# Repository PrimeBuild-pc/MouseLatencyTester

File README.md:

<div align="center">

<br>

<br>

**Measure how long your mouse actually takes to click — to the microsecond.**

A Teensy 2.0 watches a probe touch the switch, the dashboard watches Windows report the click,<br>
and the difference is your real input latency. Archive it, chart it, compare it.

<br>

<sub>No hardware yet? The app ships a built-in simulator — <b>Settings → Demo mode</b>.</sub>

</div>

<br>

---

## Prototype A1 PCB

The [compact BPV10 PCB documentation](docs/hardware/README.md) includes the KiCad design,
schematic, fabrication files, BOM and assembly instructions. The new optical board is an
**unbuilt prototype**: electrical/layout checks pass, but physical validation, comparator
firmware and the enclosure are still pending. This is separate from the existing assembled
tester described below.

<table>
<tr>
<td width="50%" align="center">
<br>
<sub><b>Top</b> — OPA380 TIA, TLV3501 comparator, threshold trimmer, BTN1/BTN2</sub>
</td>
<td width="50%" align="center">
<br>
<sub><b>Bottom</b> — the BPV10 photodiode faces the monitor</sub>
</td>
</tr>
</table>

<div align="center">
<sub><b>KiCad 3D render of the A1b design (56 × 48 mm), not a photo:</b> the board has not been built or tested yet.
The Teensy 2.0 has no 3D model, so only its header pads show; the photodiode is drawn with a generic 5 mm LED model.
Flat <a href="docs/images/hardware/pcb-a1b-top.png">top</a> and <a href="docs/images/hardware/pcb-a1b-bottom.png">bottom</a> views and a
<a href="hardware/compact/mechanical/mouse_latency_tester.step">STEP model</a> for the enclosure are in the repo.</sub>
</div>

## Gallery

<div align="center">

<sub><b>Live test</b> — mean, median, P5/P95/P99, IQR, MAD and jitter, with outliers ringed on the chart.</sub>

</div>

<br>

<table>
<tr>
<td width="50%" align="center">
<br>
<sub><b>Compare</b> — box plot with baseline deltas in ms and %</sub>
</td>
<td width="50%" align="center">
<br>
<sub><b>ECDF</b> — where the slow clicks actually live</sub>
</td>
</tr>
<tr>
<td width="50%" align="center">
<br>
<sub><b>Test mode</b> — 🟩 armed, press now</sub>
</td>
<td width="50%" align="center">
<br>
<sub><b>Test mode</b> — 🟥 wait / release</sub>
</td>
</tr>
</table>

<details>
<summary><b>More screenshots</b> — light theme, sessions, devices, settings, raw samples, histogram</summary>
<br>
<table>
<tr>
<td width="50%" align="center">
<br>
<sub>Live test — light theme</sub>
</td>
<td width="50%" align="center">
<br>
<sub>Sessions — searchable archive</sub>
</td>
</tr>
<tr>
<td width="50%" align="center">
<br>
<sub>Compare — raw samples</sub>
</td>
<td width="50%" align="center">
<br>
<sub>Compare — histogram</sub>
</td>
</tr>
<tr>
<td width="50%" align="center">
<br>
<sub>Devices — one profile per mouse</sub>
</td>
<td width="50%" align="center">
<br>
<sub>Settings — theme, language, one-click update</sub>
</td>
</tr>
<tr>
<td colspan="2" align="center">
<br>
<sub>Test mode — 🟦 target reached</sub>
</td>
</tr>
</table>
</details>

<sub>Screenshots are taken in demo mode, which is why they carry the simulated-data banner.</sub>

---

## What this actually measures

A metal probe is clamped so that it touches a strip of copper tape on the mouse button at the exact
instant the switch actuates. That contact closure is **t₀**, taken inside an interrupt on the Teensy.
The mouse then sends its HID report, Windows delivers the click, and the dashboard answers the
Teensy — **t₁**. The calibrated serial round-trip is subtracted from `t₁ − t₀`.

The result covers switch debounce, the mouse's internal processing, the wireless or USB link, the
polling interval and the OS input stack. It does **not** cover display or render latency.

> [!IMPORTANT]
> **The method is completely non-invasive.** The mouse is never opened, nothing is soldered to its
> PCB, and no transistor is wired across its microswitch. The only mouse-side modification is a
> strip of **removable** conductive copper tape on the outside of the left button. Peel it off and
> the mouse is exactly as it was.

### Where the project is

**The KY-018 build is finished and it works.** Every part of it is built, wired and verified on the
bench, and every release ships against it. Nothing in the table below is waiting on hardware.

**A second front-end is being built** — a BPV10 photodiode with a transimpedance amplifier and a
comparator, replacing the photoresistor. It is **designed, not assembled**: no firmware talks to it
yet and no measurement in this repository comes from it. It matters because it moves `t₁` from a
software threshold on a sampled ADC value to a **hardware interrupt**, which takes the sensor's own
response out of the measurement — on a 360 Hz OLED the KY-018 is now the largest unknown left in
the chain. Design and BOM: **[docs/optical_front_end.md](docs/optical_front_end.md)**.

An **enclosure** is the other open item: a 3D-printed box for the whole thing, with a mount that
holds the probe steady. That one changes no measurement. The compact board's
[STEP model](hardware/compact/mechanical/mouse_latency_tester.step) is its starting point.

#### Feature maturity

| | Feature | Status |
|---|---|---|
| 1 | **Probe method** — the measurement above | ✅ **Working and verified on real hardware.** Every number the app produces comes from this path |
| 2 | **OLED SH1106** | ✅ Working. Frozen during test mode so I²C traffic cannot disturb the timing |
| 3 | **KY-018 light sensor** | ✅ Working, but **telemetry only**. Recorded with each run; it plays no part in any measurement |
| 4 | **BTN1 / BTN2 buttons** | ✅ **Working. 10/10 acceptance test passed on hardware.** BTN1 enters/leaves test mode, BTN2 clears the live run outside test mode. Presses are still counted and logged |
| 5 | **Probe-to-Photon mode** | ✅ **Working, firmware v1.5.** Separate mode, own calibration, own metric. Verified on hardware: 40 clicks, ~16 ms median against ~3 ms on the same mouse in Probe-to-PC. Accuracy is limited by the KY-018 — [read this](#probe-to-photon) before quoting a number |
| 6 | **Frame cap on the optical target** | ✅ Working. 30 / 60 / 120 / 240 / 360 / 500 / 1000 fps, or follow the monitor. Recorded with the run |
| 7 | **Photodiode front-end** (BPV10 + OPA380 + TLV3501) | 🚧 **Designed, not built.** Would make `t₁` a hardware interrupt instead of a sampled threshold — [design](docs/optical_front_end.md) |
| 8 | **In-game measurement** | 📋 Planned, and it needs row 7 first. Visible but disabled in the mode picker |

Rows 1–6 are built and verified. There is no component in this project that is wired but unused, and
none that is listed but unwired.

---

## Install

<table>
<tr>
<td width="55%" valign="top">

### Windows installer &nbsp;<sub>recommended</sub>

Grab **`LatencyTester-<version>-Setup.exe`** from the
[latest release](https://github.com/PrimeBuild-pc/MouseLatencyTester/releases/latest).

It installs the dashboard, **the firmware sketches** and the full documentation
into a single folder, so you can flash the Teensy without cloning anything.

- Per-user install by default — **no admin rights needed**
- Your archive lives in `Documents\LatencyTester\` and is **never** touched by the uninstaller
- Built-in **one-click updater**: *Settings → Check for updates*

<sub>The installer is not code-signed, so SmartScreen warns on first run.
Verify <code>SHA256SUMS.txt</code> from the release.</sub>

</td>
<td width="45%" valign="top">

### From source

```powershell
git clone https://github.com/PrimeBuild-pc/MouseLatencyTester.git
cd MouseLatencyTester
pip install -r requirements.txt
python run_dashboard.py
```

### No hardware?

**Settings → Demo mode → Start demo device.**

A simulator that speaks the real serial protocol drives the whole interface,
the charts and the archive. Runs saved that way are flagged `[DEMO]` and never
mixed with real measurements.

</td>
</tr>
</table>

### Languages

<div align="center">

🇬🇧 English &nbsp;·&nbsp; 🇮🇹 Italiano &nbsp;·&nbsp; 🇩🇪 Deutsch &nbsp;·&nbsp; 🇪🇸 Español &nbsp;·&nbsp; 🇫🇷 Français &nbsp;·&nbsp; 🇯🇵 日本語 &nbsp;·&nbsp; 🇷🇺 Русский &nbsp;·&nbsp; 🇨🇳 中文

</div>

Switch under *Settings → Language*; the choice persists. Adding another is a single JSON file and
**no Python at all** — see [CONTRIBUTING.md](CONTRIBUTING.md#adding-a-language).

### Documentation

[Installation](docs/installation_windows.md) &nbsp;·&nbsp;
[Flashing the Teensy](docs/flashing_teensy.md) &nbsp;·&nbsp;
[Bring-up & electrical notes](docs/wiring.md) &nbsp;·&nbsp;
[First measurement](docs/first_test.md) &nbsp;·&nbsp;
[Troubleshooting](docs/troubleshooting.md) &nbsp;·&nbsp;
[Serial protocol](docs/serial_protocol.md)

---

## The dashboard

<table>
<tr>
<td width="33%" valign="top">

#### 📊 Live test
Mean, median, min, max, std dev, P5/P95/P99, IQR, MAD and jitter (P95−P5).
Live chart with outliers ringed, `BTN1`/`BTN2` counters, and a **Measure**
button for the real polling rate.

</td>
<td width="33%" valign="top">

#### 🗂 Sessions
Searchable archive. Rename, edit metadata, **duplicate as a template** for the
next configuration, export to CSV.

</td>
<td width="33%" valign="top">

#### 📈 Compare
Raw samples, box plot, ECDF or histogram. Selectable **baseline** with
Δ median / mean / P95 / P99 in ms and %. Export to PNG, SVG, PDF.

</td>
</tr>
<tr>
<td valign="top">

#### 🖱 Devices
One profile per mouse: manufacturer, model, serial, switch type, usual
firmware, notes. **Detects the connected mouse** and reconnects it to its
saved profile automatically.

</td>
<td valign="top">

#### ⚙️ Settings
Eight languages, light / dark / system theme, archive backup, demo mode and
**one-click update**. Preferences persist.

</td>
<td valign="top">

#### 🎯 Test mode
Full screen, colour-coded: 🟩 press · 🟥 wait · 🟦 done. The OLED is frozen so
the display never disturbs the timing.

</td>
</tr>
</table>

> [!IMPORTANT]
> **Raw data is never discarded.** Outliers are detected with the Tukey fence and **marked**, not
> removed. They stay in the database, in the CSV export and in every statistic. Deciding what an
> outlier means is the operator's job, not the software's.

### Knowing your mouse

**Name** — *Devices → Detect connected mouse* reads the USB descriptor and fills in the name,
manufacturer and serial. That name is often the internal or dongle name rather than the marketing
one (an ATK F1 reports as `Compx Wireless mouse 8k dongle-L`), so **rename it to whatever you
like** — the profile is linked to the device by its `VID:PID` hardware ID, not by its name. Once
linked, plugging that mouse in selects its profile automatically.

**Polling rate** — *Live test → Measure* counts the mouse's actual Raw Input reports for two
seconds while you move it, and fills the field with the nearest standard rate while reporting what
was really counted. It measures what the mouse **achieves**, which is not always what it is
configured for. If you do not move enough, it says so rather than guessing.

**DPI** — not detectable, and not faked. No Windows API exposes it: DPI lives inside the mouse and
vendor software reads it over undocumented, per-manufacturer HID reports. Type it in from your
mouse's own software.

### A typical session

```
Razer Viper → 1000 Hz → 50 samples → Save → New run
Razer Viper → 2000 Hz → 50 samples → Save → New run
Razer Viper → 4000 Hz → 50 samples → Save → New run
Razer Viper → 8000 Hz → 50 samples → Save
→ Compare, baseline = 1000 Hz
```

All without restarting the program.

---

## Hardware

Everything below describes the build that is **physically assembled and verified**, so it can be
reproduced without any prior context.

<details open>
<summary><b>BOM / parts list</b></summary>
<br>

| Qty | Component | Function | Notes |
|:--:|---|---|---|
| 1 | **Teensy 2.0** (ATmega32U4, 16 MHz) | Takes t₀ in an ISR, computes latency, talks to the PC | The whole measurement lives here |
| 1 | **OLED 1.30", 128×64, SH1106, I²C, 4-pin** | Local status display | Address `0x3C`. **One** display — see note below |
| 1 | **KY-018 photoresistor module** | `LIGHT` telemetry recorded with each run | Analog output. Not part of the measurement |
| 2 | **Momentary push buttons, 4-pin** | `BTN1` / `BTN2` | Used as plain switches to GND. No external resistors — `INPUT_PULLUP` is used. **Wire diagonally** — see below |
| 1 | **Breadboard** (400 or 830 points) | Power rails and module mounting | |
| 1 | **Conductive copper tape**, 5 mm | Contact pad on the **outside** of the mouse button | Removable. Aluminium foil + tape works too |
| 1 | **Metal probe / multimeter tip** | Closes the circuit at the instant of the click | A stiff bare wire also works |
| 1 | **Helping hands / third hand** | Holds the probe steady | Not optional in practice — probe alignment is the biggest error source |
| — | **Jumper wires M-M and M-F** | Wiring | Both types needed |
| — | **Solid-core wire** | Short, tidy breadboard runs | |
| — | **Soldering iron + solder** | Permanent joints on the probe lead and the tape lead | **Never used on the mouse itself** |
| — | **Insulating tape** | Strain relief and shorts prevention | |
| 1 | **Micro USB cable** | Power and serial | A data cable, not charge-only |

> [!NOTE]
> An earlier version of this project's parts list mentioned *two* OLED displays as a future upgrade.
> **The validated build uses exactly one.** A second display is not required and is not supported.

> [!IMPORTANT]
> **The 4-pin buttons are just switches.** A tactile 4-pin button has **two internal pairs**: the
> two legs on the *same side* are permanently joined to each other. Take one leg from **one side**
> and one from the **opposite** side — the diagonal — so that pressing actually closes the circuit.
>
> Wire that diagonal between the Teensy pin and **GND**, nothing else. Straddle the breadboard's
> centre groove so the two pairs land on different rows. Check with a continuity tester: **open at
> rest, closed when pressed.** If it beeps at rest you took two legs of the same pair, and the pin
> sits permanently at GND — the firmware reads it as "already pressed" at boot and no press event
> will ever appear.

Measured on USB power: **≈ 4.8 V** between `VCC` and `GND` at the breadboard rails.

This is the complete parts list. Everything in it is in the built tester, and nothing else is
needed.

</details>

<details open>
<summary><b>Wiring — pin by pin</b></summary>
<br>

| Component | Component pin | Teensy pad | Arduino pin | Wire colour | Function |
|---|---|:--:|:--:|---|---|
| Breadboard rail | + | `VCC` | — | 🔴 Red | Power to OLED and KY-018 (~4.8 V on USB) |
| Breadboard rail | − | `GND` | — | ⚫ Black | Common ground for everything |
| Probe | tip | `D2` | **7** | ⚪ White | Probe input, `INPUT_PULLUP`, trigger on `FALLING` |
| Copper tape | on left mouse button | `GND` | — | ⚫ Black | Return path — closing to GND is the t₀ event |
| OLED SH1106 | `GND` | `GND` | — | ⚫ Black | Ground |
| OLED SH1106 | `VCC` / `VDD` | `VCC` | — | 🔴 Red | Power |
| OLED SH1106 | `SCL` / `SCK` | `D0` | **5** | 🟡 Yellow | I²C clock |
| OLED SH1106 | `SDA` | `D1` | **6** | 🟢 Green | I²C data |
| KY-018 | `S` | `F0` | **A0** | 🔵 Blue | Analog light level, 0–1023. `LIGHT` telemetry **and** the Probe-to-Photon `t₁` |
| KY-018 | `+` | `VCC` | — | 🔴 Red | Power |
| KY-018 | `−` | `GND` | — | ⚫ Black | Ground |
| BTN1 | one corner | `B0` | **0** | 🟠 Orange | Button input, `INPUT_PULLUP` |
| BTN1 | **opposite** corner | `GND` | — | ⚫ Black | Pressed = LOW. Diagonal, never the same side |
| BTN2 | one corner | `B1` | **1** | 🟣 Purple | Button input, `INPUT_PULLUP` |
| BTN2 | **opposite** corner | `GND` | — | ⚫ Black | Pressed = LOW. Diagonal, never the same side |
| Built-in LED | — | `D6` | **11** | — | Lit while a measurement is pending |

> [!WARNING]
> **KY-018 pin order:** always follow the `S` / `+` / `−` markings printed on the module.
> **Do not infer the order from the physical pin positions** — it varies between manufacturers.

> [!TIP]
> **`A0` on a Teensy 2.0** resolves to pad `F0` (digital 21) in Teensyduino. That is why the
> sketch's `analogRead(A0)` reads the pad labelled `F0`.

</details>

<details>
<summary><b>Wire colour convention</b></summary>
<br>

| Colour | Use |
|---|---|
| ⚫ Black | GND |
| 🔴 Red | VCC / ≈ 5 V |
| 🟡 Yellow | OLED `SCL` |
| 🟢 Green | OLED `SDA` |
| 🔵 Blue | KY-018 analog signal (`LIGHT` telemetry and the Probe-to-Photon `t₁`) |
| ⚪ White | Probe |
| 🟠 Orange | BTN1 |
| 🟣 Purple | BTN2 |

**These colours are a project convention for readability, not an electrical requirement.** Any
colour works electrically; keeping to the table makes the photos, the diagrams and the physical
build agree with each other.

</details>

<details>
<summary><b>Diagram</b></summary>
<br>

```text
                    TEENSY 2.0  (ATmega32U4, 16 MHz)
                  +--------------------------------+
   metal probe ---|  D2   (7)   probe in    [WHT]  |
        :         |                                |
        :         |  D0   (5)   I2C SCL     [YEL] -+--------> OLED SCL
        :         |  D1   (6)   I2C SDA     [GRN] -+--------> OLED SDA
        :         |                                |
        :         |  F0   (A0)  analog in   [BLU] <+--------- KY-018  S
        :         |             (t1 in Probe-to-Photon)             
        :         |                                |
        :         |  B0   (0)   BTN1 in     [ORG] <+--------- BTN1 --+
        :         |  B1   (1)   BTN2 in     [PUR] <+--------- BTN2 --+
        :         |                                | (4-pin buttons: |
        :         |                                |  wire DIAGONAL  |
        :         |                                |  corners only)  |
        :         |                                |                 |
        :         |  D6   (11)  built-in LED       |                 |
        :         |                                |                 |
        :         |  VCC                    [RED] -+---+--> OLED VCC |
        :         |  GND                    [BLK] -+-+ +--> KY-018 + |
        :         +--------------------------------+ |               |
        :                                            |               |
        v                                            +--> OLED GND   |
  +------------------------+                         +--> KY-018 -   |
  |  copper tape on the    |                         +---------------+
  |  LEFT mouse button     |---------[BLK]-----------+  (BTN1/BTN2 other leg)
  +------------------------+
                                    GND rail

  The probe touches the tape at the exact instant the switch actuates -> t0.

  Colour codes: BLK=GND  RED=VCC  YEL=SCL  GRN=SDA
                BLU=KY-018 signal  WHT=probe  ORG=BTN1  PUR=BTN2

  Nothing is wired to the mouse other than removable copper tape on the outside
  of the left button.
```

```mermaid
graph LR
    subgraph Teensy["Teensy 2.0 · ATmega32U4"]
        VCC["VCC"]
        GND["GND"]
        D2["D2 · pin 7"]
        D0["D0 · pin 5"]
        D1["D1 · pin 6"]
        F0["F0 · A0"]
        B0["B0 · pin 0"]
        B1["B1 · pin 1"]
        LED["D6 · pin 11 · LED"]
    end

    PROBE["Metal probe"] -->|white| D2
    TAPE["Copper tape<br/>on left mouse button"] -->|black| GND

    D0 -->|yellow · SCL| OLED["OLED SH1106<br/>128x64 I2C 0x3C"]
    D1 -->|green · SDA| OLED
    VCC -->|red| OLED
    GND -->|black| OLED

    KY["KY-018 LDR module"] -->|blue · S| F0
    VCC -->|red · +| KY
    GND -->|black · −| KY

    BTN1["BTN1<br/>4-pin, diagonal"] -->|orange| B0
    BTN1 -->|black| GND
    BTN2["BTN2<br/>4-pin, diagonal"] -->|purple| B1
    BTN2 -->|black| GND

```

This is the whole tester. There is no unwired component and nothing left to connect.

</details>

<details>
<summary><b>Bring-up — test in this order</b></summary>
<br>

Each step must pass before moving to the next.

| # | Step | Expected result |
|:--:|---|---|
| 1 | **Teensy alone.** Flash, open Serial Monitor at 115200 | `LATENCY_TESTER v1.5 OLED+LDR+BTN+PHOTON` then `READY`. **The Teensy does not reset when the monitor opens**, so send `V` if the banner has already scrolled past |
| 2 | **Probe.** Touch the probe to the copper tape | `TRIG` appears, pin-11 LED lights. Without the dashboard you then get `TIMEOUT:…` — that is correct |
| 3 | **OLED I²C scan** | Exactly one device at `0x3C` |
| 4 | **OLED display test** — `firmware/displayTester/` | Text on the panel; the main sketch prints `OLED_OK:0x3C` |
| 5 | **KY-018.** Send `L`, or read `LIGHT` in the Live tab | Covered ≈ **0–20**, evening room ≈ **150–250**, phone torch ≈ **1000**. If it does not move, the module is miswired |
| 6 | **All three together** | Probe still triggers; display refreshes ~2×/s. Occasional `SKIP:OLED_REFRESH` outside test mode is normal and correct |
| 7 | **Calibration** | `CALIB_OK:<offset>,…`. Lands near 250 µs — see the [known quirk](docs/serial_protocol.md#6-calibration-sequence) |
| 8 | **Test mode** | Overlay appears, `TESTMODE:ON`, OLED freezes, green ⇄ red tracks `ARMED`/`REARM` |
| 9 | **BTN1 / BTN2** | 10 presses → **exactly 10** events, no phantoms, no doubles, no repeat while held. Then BTN1 enters/leaves test mode and BTN2 clears the run outside it |
| 10 | **Probe-to-Photon** | Aim the KY-018 at the target, calibrate black then white, and check the separation is accepted. Then 10 presses → 10 `OPT:` samples |
| 11 | **Done** | That is the whole bring-up. Nothing else needs wiring |

Full detail with expected values: **[docs/wiring.md](docs/wiring.md)**.

</details>

<details>
<summary><b>Electrical notes</b></summary>
<br>

- **Disconnect USB before soldering.** No exceptions.
- **Never connect VCC directly to the probe signal.** `D2` is an input with an internal pull-up; it
  expects to be shorted to **GND** and nothing else.
- **All modules share a common GND.** Teensy, OLED, KY-018 and both buttons on the same rail.
- **Follow the printed `S` / `+` / `−` labels on the KY-018.** Do not deduce from pin position.
- **No external resistors on the buttons.** `INPUT_PULLUP` provides them; pull-downs break the logic.
- **Never modify the mouse.** No opening it, no soldering to its PCB, no transistor across its
  microswitch. Removable copper tape on the outside of the button is the only mouse-side change.
- Measured supply on USB: **≈ 4.8 V**. Both the OLED and the KY-018 are fine at that level.

</details>

---

## Probe-to-Photon

A **second, separate** measurement mode, firmware **v1.5**. Probe-to-PC is untouched by it: the
probe ISR, the `TRIG`/`H` handshake, the serial calibration, the filters, the re-arm rules and the
OLED freeze are byte-identical to v1.4 and v1.3.

### What each mode measures

| | Probe-to-PC | Probe-to-Photon |
|---|---|---|
| **t₀** | Probe contact on `D2` | Probe contact on `D2` — **the same ISR** |
| **t₁** | The dashboard answers `H` over serial | The KY-018 on `A0` crosses the calibrated threshold |
| **Covers** | Mouse + link + polling + OS input stack | The above **plus** the app, the compositor, the GPU queue and the panel |
| **Serial round-trip subtracted** | Yes, `calibration_us` | **No** — nothing is transmitted between t₀ and t₁, so there is nothing to subtract |
| **Typical figure** | single-digit ms | tens of ms |
| **Status** | ✅ verified | 🧪 works, accuracy bounded by the sensor |

### How a run works

**You do not calibrate by hand.** The calibration happens inside the full-screen overlay, on the
same target the measurement uses — a baseline sampled anywhere else describes a different patch of
screen, with a different backlight, and is worthless.

1. **Live test → Measurement mode → Probe-to-Photon.** The optical panel appears.
2. **Fix the KY-018 against the middle of the screen** — elastic bands, tape, a clamp — facing it,
   a couple of centimetres away. The target is a 620 × 440 block dead centre, so it does not need
   precise aim; it does need the sensor not to drift afterwards.
3. **Press *Calibrate on the full-screen target*.** A centred full-screen target appears, paints
   itself black, waits 400 ms for the photoresistor to settle, samples `A0` — that is `dark` — then
   does the same in white for `bright`, shows the result and closes itself. Do not move the sensor
   while it runs; it takes about a second and a half. **Entering test mode repeats it automatically**,
   so the baselines always come from the run that is about to happen.
4. **The threshold is derived automatically**: the midpoint between the two. Direction is derived
   too, so a module whose ADC value *falls* as light rises works with no setting.
5. If the two baselines are less than **60 counts** apart it stops at `CALIBRATION FAILED`, reports
   the numbers it actually measured, and **stays on screen** with a live `LIGHT` reading updating
   several times a second. Move the sensor until that number swings properly between the black and
   white phases, press <kbd>Enter</kbd> to retry, <kbd>Esc</kbd> to give up. It never arms on a bad
   calibration: a threshold inside the noise would make every sample a coin toss.
6. Otherwise the overlay hands over to the normal green/red/blue cycle with the black target in
   place. The instant Windows reports the click the target turns white; the Teensy has been sampling
   `A0` since the probe contact and stops at the first reading past the threshold.
7. Each sample arrives as `OPT:<ms>,raw:<adc>,…`. `raw` is the ADC value that tripped the threshold,
   kept per sample for debugging.

**Pick a frame cap before you start.** The optical panel offers 30 / 60 / 120 / 240 / 360 / 500 /
1000 fps and *Monitor*, which follows the detected refresh rate. The target then changes only on a
frame boundary, exactly as a game presents, so the wait for the next frame lands inside the
measurement instead of being assumed away. The cap in force is printed on the full-screen overlay
and stored with the run: the same mouse at 30 fps and at 360 fps produces two different, both
correct, results.

There is deliberately **one** calibration button and no way to sample a baseline anywhere except a
full-screen centred target: two readings from different parts of the screen describe different
patches of backlight, and a threshold built from them is worthless. To check the sensor is alive
without calibrating anything, watch the **LIGHT** field in the controls — it updates every second.

Guards, all of them deliberate: the target is a **plain label with no bindings**, so aiming the
sensor can never produce a click; a press with no calibration is refused with `OPT_ERR:NO_CAL`; a
target that is already white at t₀ is refused with `OPT_ERR:NOT_DARK` instead of returning a
near-zero time; and no transition inside **400 ms** ends in `OPT_TIMEOUT` rather than a hung
firmware.

### Read this before quoting a Probe-to-Photon number

> [!WARNING]
> **The KY-018 is a photoresistor, not an instrument.** A CdS cell's own response time is in the
> **milliseconds** — the same order of magnitude as the thing being measured — and it drifts with
> temperature and ambient light. Its contribution is inside every figure this mode reports and
> cannot be calibrated out.
>
> Use Probe-to-Photon to compare **one setup against itself**: same room, same panel, same sensor
> position, one variable changed. Do **not** publish the absolute value as a click-to-photon
> benchmark, and do not compare it against someone else's. Precision work needs a fast photodiode
> with a transimpedance amplifier.

Two smaller contributors, named so they are not mistaken for sensor error:

- **The dashboard's own repaint is inside the measurement.** The target is flipped by a 1 ms Tk
  poll, because touching a widget from the input-listener thread is not safe. That is honest —
  click-to-photon measures everything up to the photons, the application included — but it is
  a floor the method cannot go below.
- **The ADC runs faster in this mode.** The prescaler goes from /128 to /16 while the optical mode
  is active, so a reading costs ~13 µs instead of ~112 µs. It trades a little absolute accuracy for
  finer timing, which is the right way round for a threshold crossing.

Both modes are archived side by side and can be compared, but a comparison that **mixes** them says
so in the Compare tab: they do not measure the same interval, so a delta between them is not a
like-for-like figure.

A measured example, same mouse, same session: **≈ 3 ms** in Probe-to-PC, **≈ 16 ms** in
Probe-to-Photon over 40 clicks. The ~13 ms difference is the application's repaint, the compositor,
the GPU queue, the panel — **and the KY-018's own response**, which cannot be separated out from it.
Read the difference as "this whole chain, including my sensor", never as "my monitor adds 13 ms".

---

## Firmware

| Sketch | Notes |
|---|---|
| `latency_tester/` | v1.0 — probe only |
| `latency_tester_oled_ldr/` | v1.1 — adds OLED + KY-018 |
| `latency_tester_oled_ldr_v1_2/` | v1.2 — adds `SKIP:OLED_REFRESH` |
| `latency_tester_oled_ldr_v1_3/` | v1.3 — debounce/re-arm, test mode, OLED freeze. **Measurement baseline** |
| `latency_tester_oled_ldr_v1_4/` | v1.4 — v1.3 plus BTN1/BTN2 events. Measurement path byte-identical to v1.3 |
| **`latency_tester_photon_v1_5/`** | **v1.5 — current. v1.4 plus Probe-to-Photon. The Probe-to-PC path is byte-identical to v1.4** |
| `displayTester/` | Standalone OLED check |

Older sketches still work; unknown tokens are logged, never dropped. Compatibility table in
[docs/serial_protocol.md](docs/serial_protocol.md).

---

## Repository layout

```
latency_tester/          the dashboard, as a package
  protocol.py            wire format, both modes, optical threshold maths
  constants.py           choice lists and the two measurement-mode ids
  stats.py               percentiles, MAD, outliers, deltas  (pure functions)
  database.py            SQLite archive + schema migrations
  serial_service.py      reader thread, TRIG/click association
  devices.py             mouse identification + report-rate measurement
  updater.py             checksum-verified one-click update
  demo.py                simulated Teensy, both measurement modes
  settings.py            persisted preferences
  i18n.py                translation loader
  locales/               one JSON file per language
  theme.py               light / dark / system palettes
  widgets.py             tooltips, metric cards, live chart
  export.py              CSV
  app.py                 shell, state, event pump
  views/                 live · sessions · compare · devices · preferences · testmode
firmware/                Arduino sketches, v1.0 → v1.5
hardware/                compact A1 PCB, schematic, local libraries and checks
outputs/                 checked A1 fabrication ZIPs and portable KiCad project
packaging/               PyInstaller spec, Inno Setup script, build script
tests/                   pytest suite
docs/                    protocol, install, bring-up, first test, troubleshooting,
                         photodiode design and hardware/ research (not built yet)
legacy/                  the previous single-file dashboards, still runnable
```

The measurement and serial logic never imports tkinter, which is what lets it be tested headlessly.

## Development

```powershell
pip install -r requirements-dev.txt
python -m pytest tests -q
```

**293 tests**, **88% coverage of the non-GUI code** — the GUI is deliberately excluded rather than
padded with tests that assert nothing. CI enforces the coverage floor, so the badge cannot drift
down silently.

Covered: protocol parsing including the button tokens, the firmware button-debounce rules,
statistics and percentiles, the database and its migrations, run save/load/duplicate, CSV export,
settings, every locale, the updater's checksum verification and host allow-listing, mouse naming
rules and the polling-rate formula, the TRIG↔click association, and the demo device.

`tests/test_button_debounce.py` mirrors `serviceButtons()` / `flushButtonEvents()` from the v1.4
sketch line for line, so the bench acceptance rules are checked in CI. It is a **mirror, not an
import**: if the `.ino` changes, change the test too.

`tests/test_button_actions.py` is the opposite: it calls the dashboard's real button dispatcher on a
stub, so the refusal rules (disconnected, calibrating, `BTN2` during test mode, the confirmation
preference) are checked without needing a window.

`tests/test_photon.py` covers Probe-to-Photon end to end short of the hardware: the `OPT:` wire
format and that it can never decode as a `LAT:` one, the threshold maths including a sensor whose
value falls with light, the refusal when the two baselines are too close, and the schema-3
migration of an existing archive.

### Building the installer

```powershell
powershell -ExecutionPolicy Bypass -File packaging\build_installer.ps1
```

Requires [Inno Setup 6](https://jrsoftware.org/isdl.php). The script runs the tests first and
refuses to build if anything fails, then emits the installer and its SHA-256 into
`build\installer\`.

---

## Roadmap

The tester itself is done. What is left, in the order it makes sense to do it:

### 1. A 3D-printed enclosure

A box for the Teensy, the OLED, the KY-018 and the two buttons, with a mount that holds the probe
steady against the mouse button — probe alignment is the largest error source in the whole method,
and a printed jig fixes it better than a helping-hands clamp does. The STL will live in this
repository when it exists. It changes no measurement.

### 2. A frame-rate cap on the optical target — **done**

The target now changes only on a frame boundary, so the wait for the next frame is measured instead
of assumed — on average half a frame. Choose it per test in the optical panel: **30 / 60 / 120 /
240 / 360 / 500 / 1000 fps**, or *Monitor*, which follows the detected refresh rate. The figure
actually used is written into the run, because an archived optical number without its cap cannot be
interpreted.

Its limits, stated up front:

| Cap | Frame time | Mean added wait |
|---:|---:|---:|
| 60 fps | 16.7 ms | ≈ 8.3 ms |
| 120 fps | 8.3 ms | ≈ 4.2 ms |
| 240 fps | 4.2 ms | ≈ 2.1 ms |
| 360 fps | 2.8 ms | ≈ 1.4 ms |

The **coarse** steps are measurable; the fine ones are not. 240 → 360 is a 0.7 ms difference in the
mean, which is below the KY-018's own noise, and a Tk window throttled with `after()` has no vsync
and inherits the Windows timer granularity, so it reproduces a *cadence* rather than a real present
path. Expect it to be honest at 30/60/120 and increasingly notional above that — until the
photodiode front-end lands, at which point the sensor stops being the thing that blurs it.

One timer drives both jobs, which is also how a game loop works: input is sampled at the start of a
frame and the result is presented at the end. The schedule aims at an absolute deadline rather than
adding a rounded interval each tick, so 360 fps averages 2.78 ms instead of drifting 8% on the
3 ms rounding.

### 3. Not planned: choosing a flip model

A dropdown for Independent Flip / DirectFlip / composed flip would be a lie. The flip model is a
property of a **DXGI swap chain** plus DWM's own decision about whether the window qualifies; a
Tk window is GDI-backed and composed, and nothing in this application can select otherwise. Doing
it properly means a separate native tool with a real D3D swap chain in borderless-fullscreen or
exclusive mode — a different program, not a setting.

The same question is better answered by the next item, which uses whatever flip model the game
already uses.

### 4. In-game measurement

Calibrate the sensor on a repeatable in-game event — a muzzle flash — then measure click to flash
during normal play. This is the most useful of the four, and it wants the photodiode front-end
first: a rising edge is exactly what a comparator is for, and doing it by polling an ADC through a
photoresistor would be fighting the hardware. It is already in the mode picker, greyed out, so the
plan is visible rather than a surprise.

What makes it harder than the desktop target:

- **The scene moves.** An absolute threshold taken from one dark sample false-triggers on
  explosions, HUD flashes and ordinary brightness changes. It needs a **rising edge** with a minimum
  slope and a minimum excursion above a rolling baseline, not a fixed level.
- **Calibration becomes a ritual**: hold still without firing to capture the baseline, then fire a
  few times to capture the excursion, and derive the trigger from the two.
- **The number includes the game's weapon animation.** If a title draws the flash two frames after
  the input is consumed, those two frames are in the measurement and they are game design, not
  latency. Figures are comparable **between runs of the same weapon in the same title**, and nowhere
  else.

`t₀` does not change: it stays the probe contact in the same ISR, as it has since v1.0.

### 5. The photodiode front-end — in progress

A 360 Hz OLED settles in microseconds. The KY-018 does not: it is a photoresistor with a millisecond
response, and it is now the largest unknown in the whole chain, larger than a frame at any refresh
rate worth testing.

The replacement is designed: a **BPV10** into an **OPA380** transimpedance amplifier, then a
**TLV3501** comparator whose output goes to `D3` / digital 8 — an interrupt-capable pin. `t₁` stops
being a software threshold on a sampled ADC value and becomes a hardware interrupt, timestamped in
an ISR exactly the way `t₀` already is. `A0` keeps the analogue output for calibration and
telemetry, and is never read inside the timing window.

**Designed, not built.** Full circuit, pinouts, decoupling and BOM:
**[docs/optical_front_end.md](docs/optical_front_end.md)**. The KY-018 build stays the shipped,
verified tester until this one is assembled and measured against it.

## Contributing

Pull requests are welcome. [CONTRIBUTING.md](CONTRIBUTING.md) covers setup, testing rules and how to
add a language — the last of which needs no Python and is the easiest place to start.

One rule matters above the others: **changes to the measurement pipeline need before/after
numbers**, not opinions. Everything else is fair game.

Security issues go through
[private reporting](https://github.com/PrimeBuild-pc/MouseLatencyTester/security/advisories/new),
never a public issue — see [SECURITY.md](SECURITY.md).

## Support the project

If MouseLatencyTester is useful to you, you can support its development here:

## Privacy

No telemetry, no analytics, no background network activity. Every measurement stays in a local
SQLite file under your Documents folder. The only network request the app ever makes is the update
check, and only when **you** press the button.

## Licence

[MIT](LICENSE) © 2026 PrimeBuild.

<div align="center">
<sub>Built around a Teensy 2.0 (PJRC), with <code>pyserial</code>, <code>pynput</code> and <code>matplotlib</code>.</sub>
</div>

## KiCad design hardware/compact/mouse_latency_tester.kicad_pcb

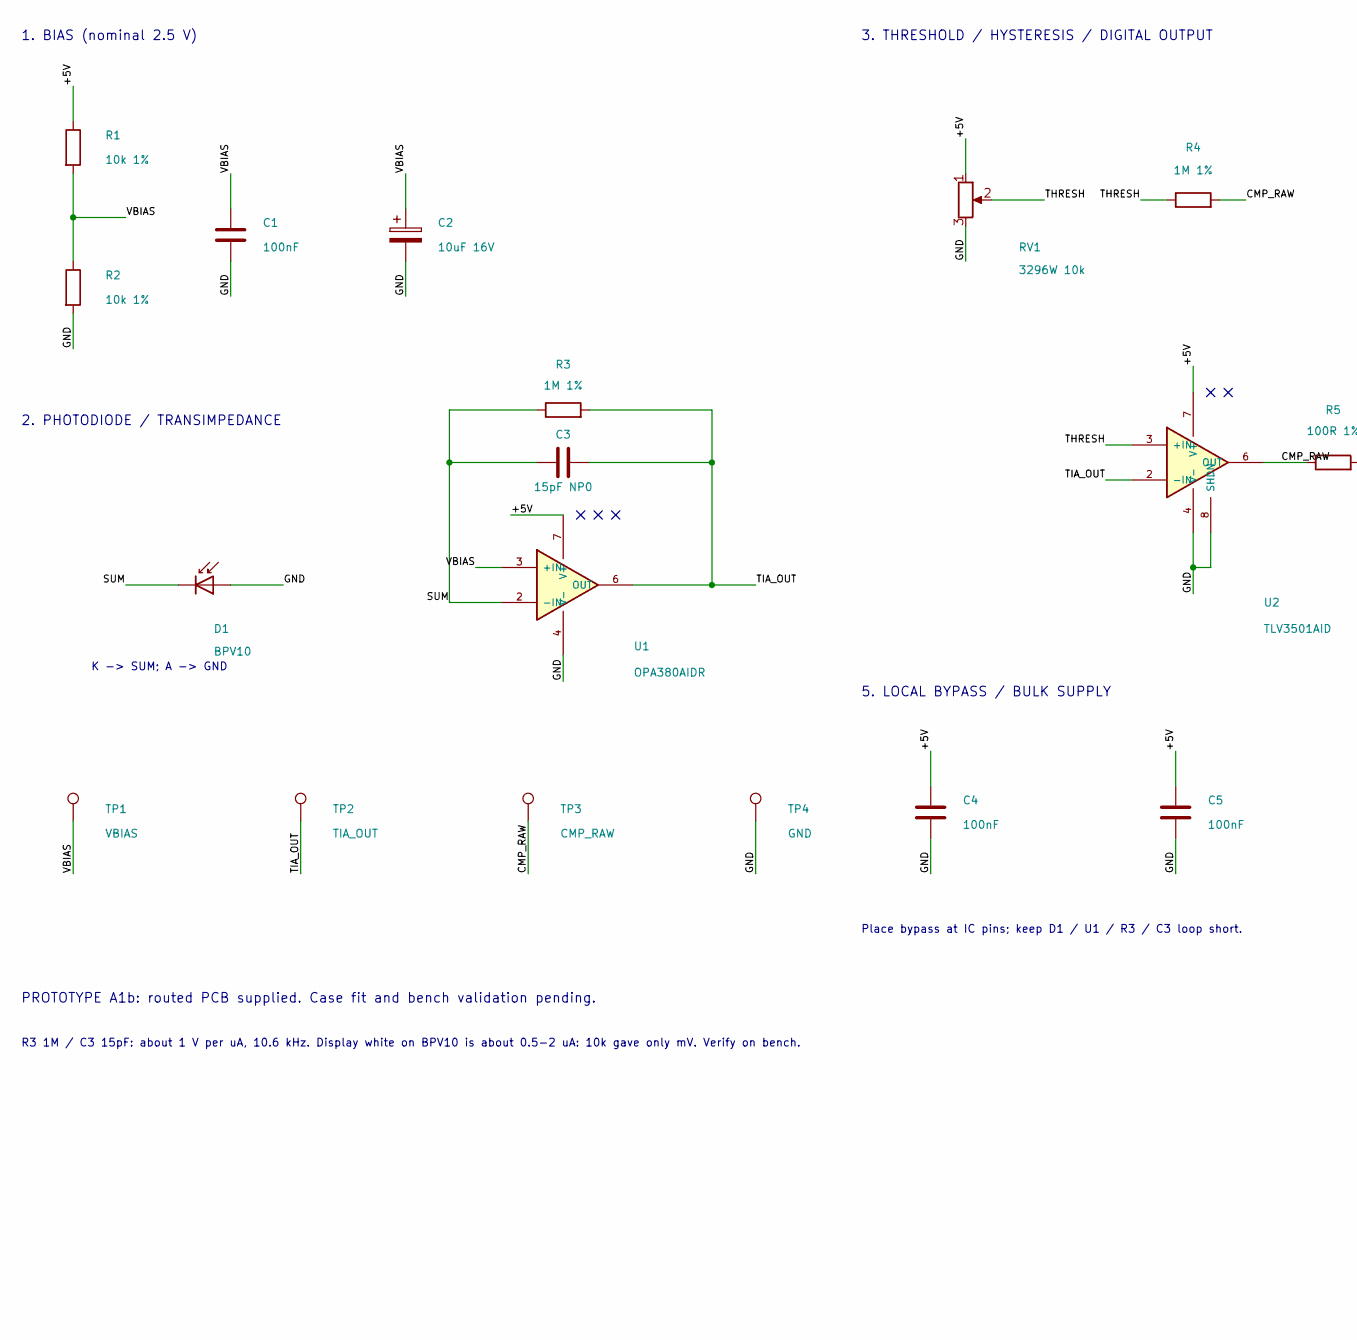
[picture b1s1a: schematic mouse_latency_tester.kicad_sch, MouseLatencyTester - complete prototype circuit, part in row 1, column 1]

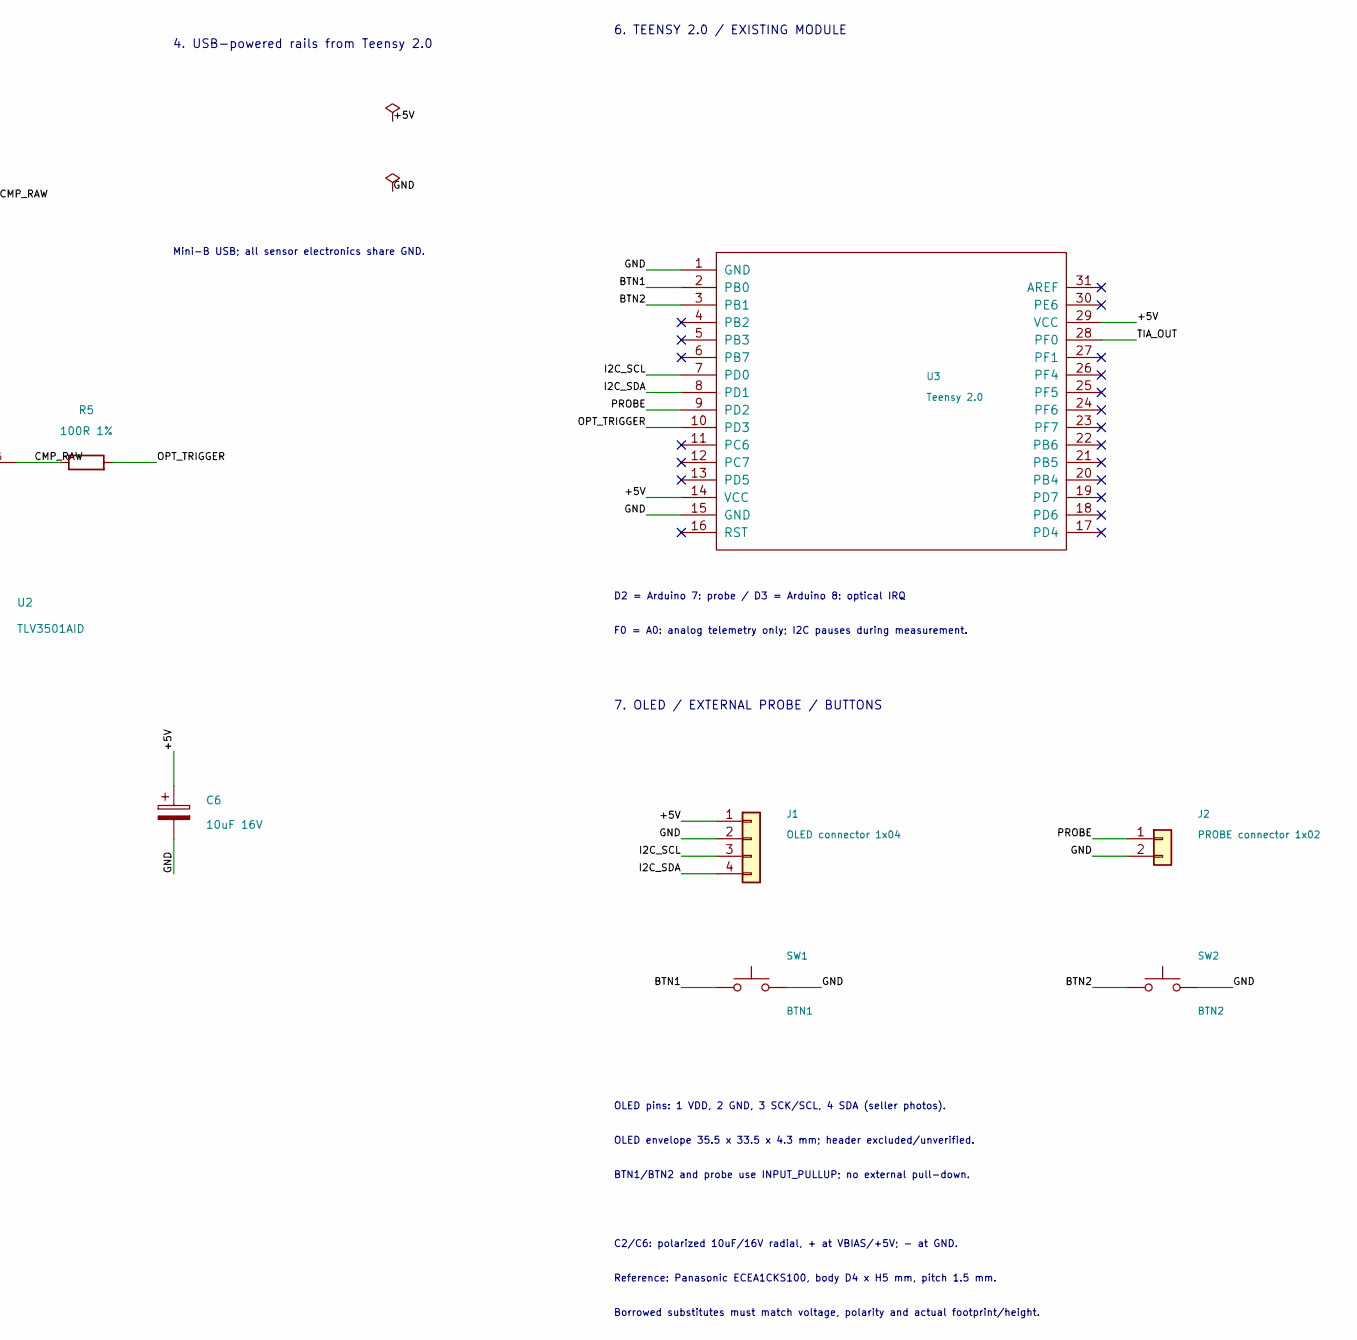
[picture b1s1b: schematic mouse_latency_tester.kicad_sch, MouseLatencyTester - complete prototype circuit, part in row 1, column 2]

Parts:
C1, C4, C5: 100nF; C_Disc_D5.0mm_W2.5mm_P2.50mm
C2, C6: 10uF 16V; CP_Radial_D4.0mm_P1.50mm; MPN ECEA1CKS100
C3: 15pF NP0; C_0805_2012Metric_Pad1.18x1.45mm_HandSolder
D1: BPV10; LED_D5.0mm; MPN BPV10
J1: OLED connector 1x04; PinHeader_1x04_P2.54mm_Vertical
J2: PROBE connector 1x02; PinHeader_1x02_P2.54mm_Vertical
R1: 10k 1%; R_Axial_DIN0207_L6.3mm_D2.5mm_P7.62mm_Horizontal
R2: 10k 1%; R_Axial_DIN0207_L6.3mm_D2.5mm_P2.54mm_Vertical
R3, R4: 1M 1%; R_Axial_DIN0207_L6.3mm_D2.5mm_P2.54mm_Vertical
R5: 100R 1%; R_Axial_DIN0207_L6.3mm_D2.5mm_P2.54mm_Vertical
RV1: 3296W 10k; Potentiometer_Bourns_3296W_Vertical
SW1: BTN1; SW_PUSH_6mm_H4.3mm
SW2: BTN2; SW_PUSH_6mm_H4.3mm
TP1: VBIAS; TestPoint_Pad_D1.5mm
TP2: TIA_OUT; TestPoint_Pad_D1.5mm
TP3: CMP_RAW; TestPoint_Pad_D1.5mm
TP4: GND; TestPoint_Pad_D1.5mm
U1: OPA380AIDR; SOIC-8_3.9x4.9mm_P1.27mm; MPN OPA380AIDR
U2: TLV3501AID; SOIC-8_3.9x4.9mm_P1.27mm; MPN TLV3501AID
U3: Teensy 2.0; Teensy2.0; MPN Teensy 2.0

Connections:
/+5V: C4.1, C5.1, C6.1, J1.1, R1.1, RV1.1, U1.7 (V+), U2.7 (V+), U3.14 (VCC), U3.29 (VCC)
/BTN1: SW1.1, U3.2 (PB0)
/BTN2: SW2.1, U3.3 (PB1)
/CMP_RAW: R4.2, R5.1, TP3.1 (1_1), U2.6 (OUT)
/GND: C1.2, C2.2, C4.2, C5.2, C6.2, D1.2 (A), J1.2, J2.2, R2.2, RV1.3, SW1.2, SW2.2, TP4.1 (1_1), U1.4 (V-), U2.4 (V-), U2.8 (SHDN), U3.1 (GND), U3.15 (GND)
/I2C_SCL: J1.3, U3.7 (PD0)
/I2C_SDA: J1.4, U3.8 (PD1)
/OPT_TRIGGER: R5.2, U3.10 (PD3)
/PROBE: J2.1, U3.9 (PD2)
/SUM: C3.1, D1.1 (K), R3.1, U1.2 (-IN)
/THRESH: R4.1, RV1.2, U2.3 (+IN)
/TIA_OUT: C3.2, R3.2, TP2.1 (1_1), U1.6 (OUT), U2.2 (-IN), U3.28 (PF0)
/VBIAS: C1.1, C2.1, R1.2, R2.1, TP1.1 (1_1), U1.3 (+IN)

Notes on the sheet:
1. BIAS (nominal 2.5 V)
2. PHOTODIODE / TRANSIMPEDANCE
K -> SUM; A -> GND
3. THRESHOLD / HYSTERESIS / DIGITAL OUTPUT
5. LOCAL BYPASS / BULK SUPPLY
Place bypass at IC pins; keep D1 / U1 / R3 / C3 loop short.
PROTOTYPE A1b: routed PCB supplied. Case fit and bench validation pending.
R3 1M / C3 15pF: about 1 V per uA, 10.6 kHz. Display white on BPV10 is about 0.5-2 uA: 10k gave only mV. Verify on bench.
4. USB-powered rails from Teensy 2.0
Mini-B USB; all sensor electronics share GND.
6. TEENSY 2.0 / EXISTING MODULE
D2 = Arduino 7: probe / D3 = Arduino 8: optical IRQ
F0 = A0: analog telemetry only; I2C pauses during measurement.
7. OLED / EXTERNAL PROBE / BUTTONS
OLED pins: 1 VDD, 2 GND, 3 SCK/SCL, 4 SDA (seller photos).
OLED envelope 35.5 x 33.5 x 4.3 mm; header excluded/unverified.
BTN1/BTN2 and probe use INPUT_PULLUP; no external pull-down.
C2/C6: polarized 10uF/16V radial, + at VBIAS/+5V; - at GND.
Reference: Panasonic ECEA1CKS100, body D4 x H5 mm, pitch 1.5 mm.
Borrowed substitutes must match voltage, polarity and actual footprint/height.

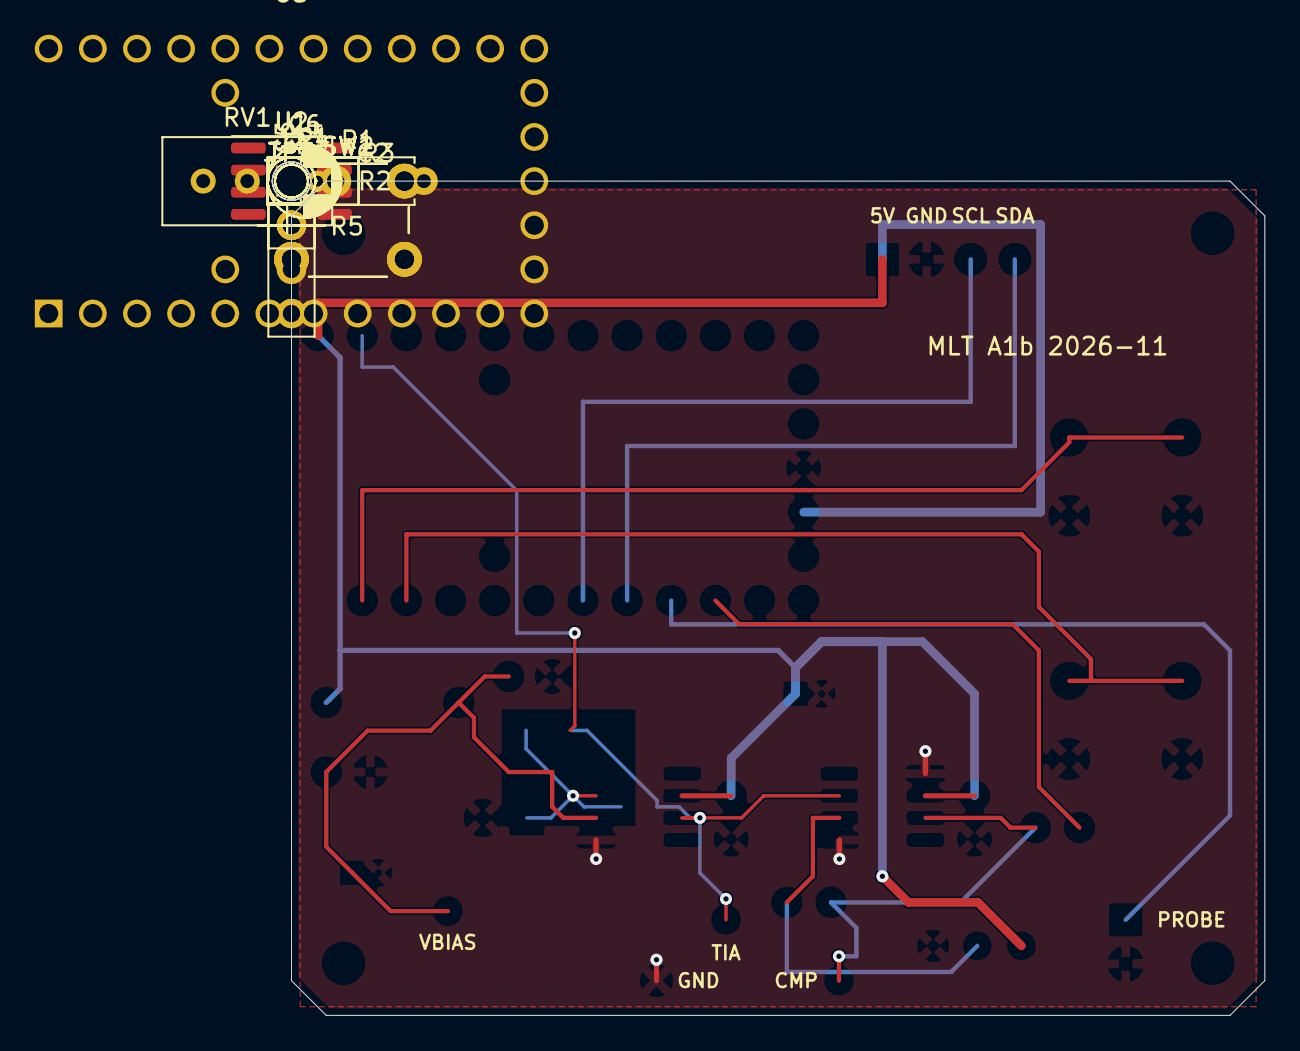
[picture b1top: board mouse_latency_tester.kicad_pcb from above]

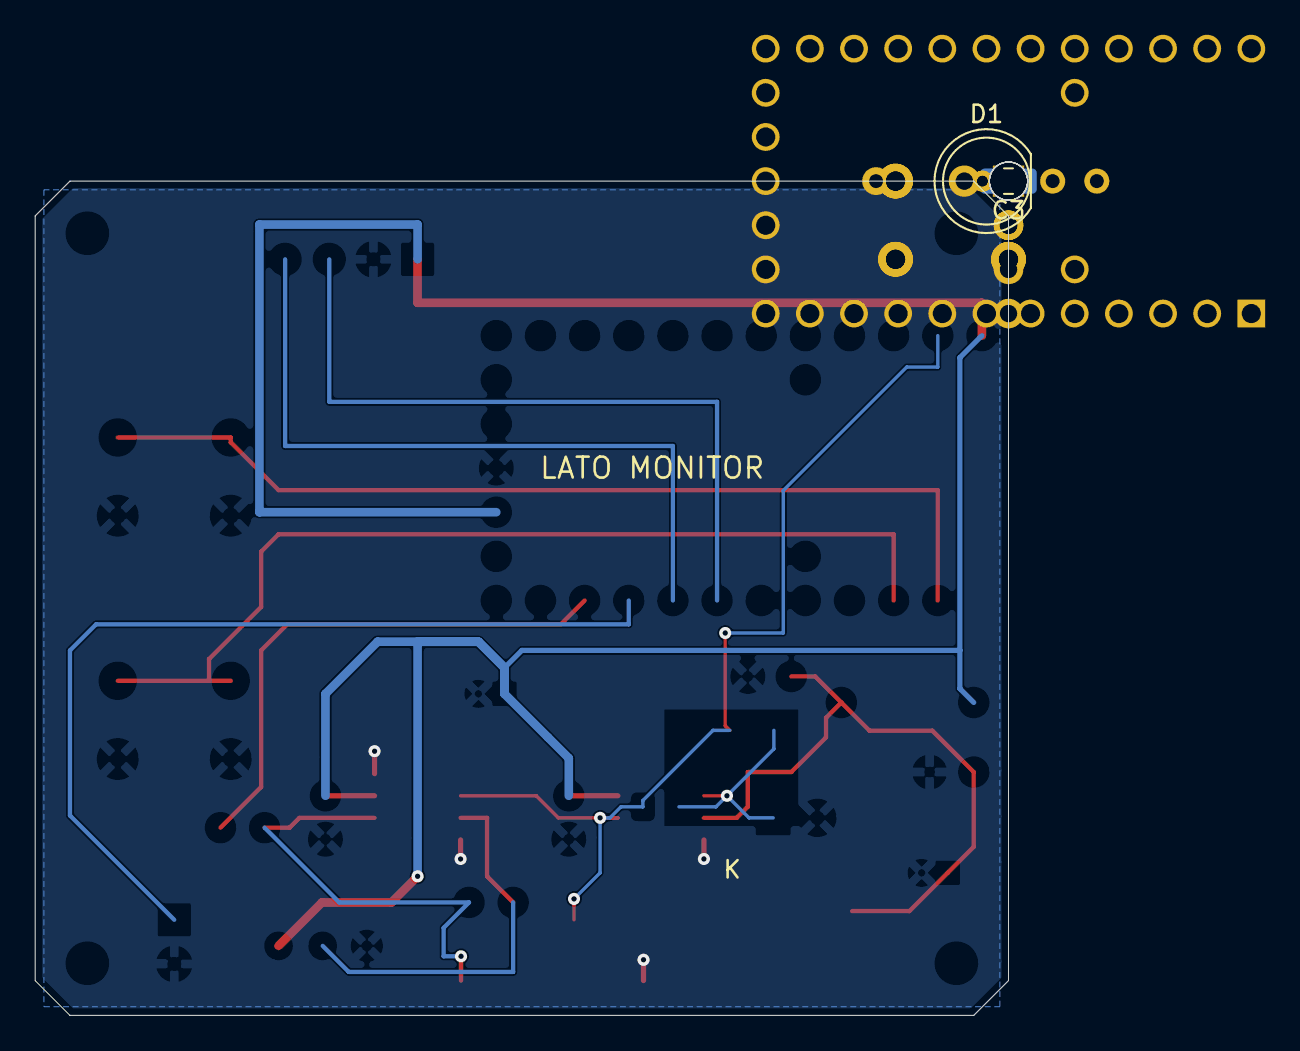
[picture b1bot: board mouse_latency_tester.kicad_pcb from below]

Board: 2 copper layers, 56.0 x 48.0 mm, 28 parts (2 on the bottom side), 13 nets.

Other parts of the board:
H1, H2, H3, H4: MountingHole_2.2mm_M2

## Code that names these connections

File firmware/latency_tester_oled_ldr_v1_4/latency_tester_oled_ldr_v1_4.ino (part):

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#include <string.h>

// ---- Pin definitions ----
#define PROBE_PIN      7      // Teensy 2.0 pad D2, interrupt-capable
#define LED_PIN        11     // Teensy 2.0 built-in LED
#define LIGHT_PIN      A0     // Teensy 2.0 pad F0
#define BTN1_PIN       0      // Teensy 2.0 pad B0, to GND
#define BTN2_PIN       1      // Teensy 2.0 pad B1, to GND

// ---- OLED ----
#define OLED_ADDR      0x3C
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#define BUTTON_COUNT        2
#define BUTTON_DEBOUNCE_MS  30

const uint8_t buttonPins[BUTTON_COUNT] = { BTN1_PIN, BTN2_PIN };
uint8_t buttonReading[BUTTON_COUNT]    = { HIGH, HIGH };  // last raw sample
uint8_t buttonStable[BUTTON_COUNT]     = { HIGH, HIGH };  // debounced level
unsigned long buttonChangedAt[BUTTON_COUNT] = { 0, 0 };
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void serviceProbeRearm() {
  if (probeArmed || measurementActive || probeFlag) return;

  if (digitalRead(PROBE_PIN) == HIGH) {
    if (probeHighSince == 0) {
      probeHighSince = millis();
    } else if (millis() - probeHighSince >= REARM_STABLE_MS) {
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
// ---- Setup ----
void setup() {
  pinMode(PROBE_PIN, INPUT_PULLUP);
  pinMode(LED_PIN, OUTPUT);
  digitalWrite(LED_PIN, LOW);

  pinMode(BTN1_PIN, INPUT_PULLUP);
  pinMode(BTN2_PIN, INPUT_PULLUP);
  // Seed the debounce state from the real pin level so a button already held
  // at power-on does not produce a phantom press.
  for (uint8_t i = 0; i < BUTTON_COUNT; i++) {
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    Serial.println("OLED_FAIL");
  }

  attachInterrupt(digitalPinToInterrupt(PROBE_PIN), probeISR, FALLING);
}

// ---- Main loop ----
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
